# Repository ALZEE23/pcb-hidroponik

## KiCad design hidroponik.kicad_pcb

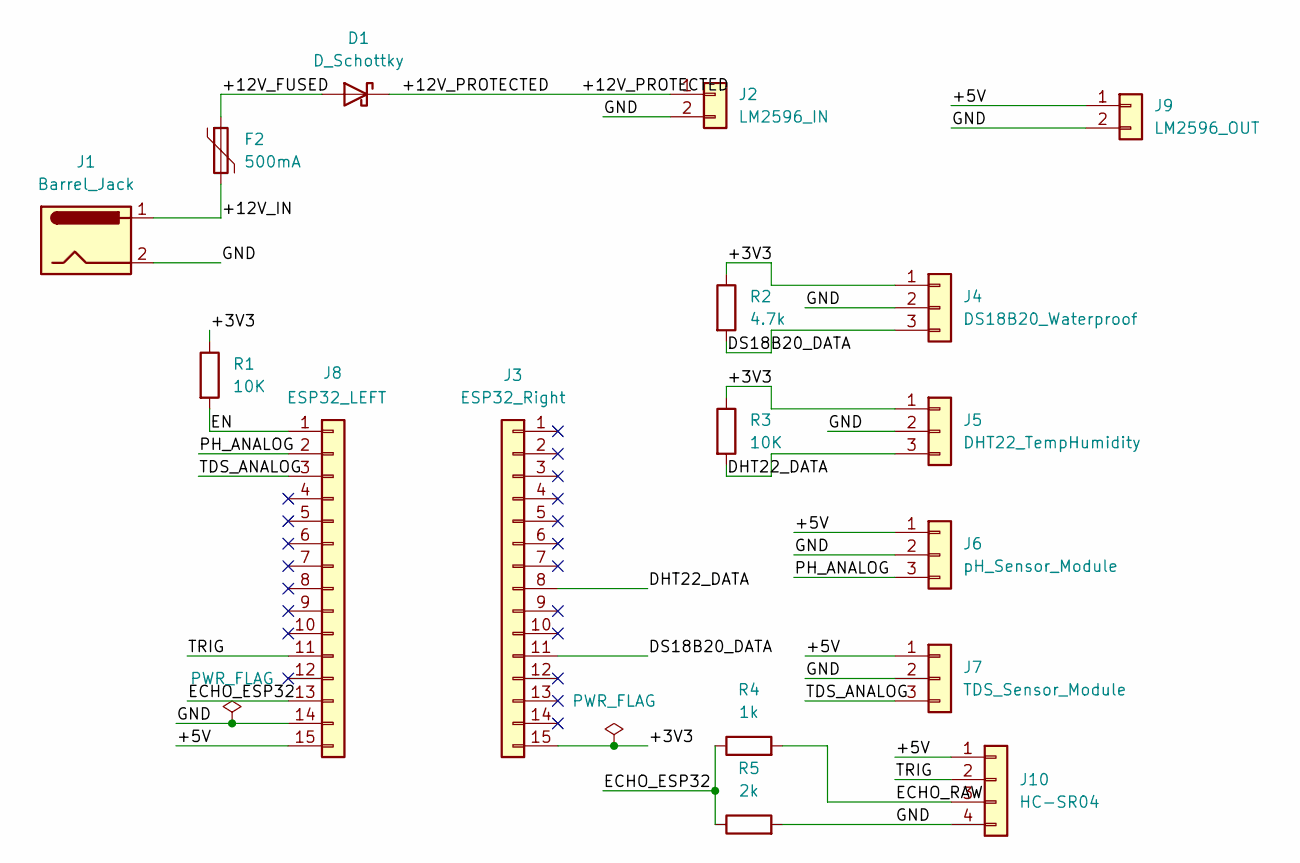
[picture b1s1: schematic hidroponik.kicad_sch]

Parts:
D1: D_Schottky; D_DO-41_SOD81_P10.16mm_Horizontal
F2: 500mA; Fuse_Bourns_MF-RG300
J1: Barrel_Jack; BarrelJack_CUI_PJ-102AH_Horizontal
J2: LM2596_IN; PinHeader_1x02_P2.54mm_Vertical
J3: ESP32_Right; PinSocket_1x15_P2.54mm_Vertical
J4: DS18B20_Waterproof; PinHeader_1x03_P2.54mm_Vertical
J5: DHT22_TempHumidity; PinHeader_1x03_P2.54mm_Vertical
J6: pH_Sensor_Module; PinHeader_1x03_P2.54mm_Vertical
J7: TDS_Sensor_Module; PinHeader_1x03_P2.54mm_Vertical
J8: ESP32_LEFT; PinSocket_1x15_P2.54mm_Vertical
J9: LM2596_OUT; PinHeader_1x02_P2.54mm_Vertical
J10: HC-SR04; PinHeader_1x04_P2.54mm_Vertical
R1, R3: 10K; R_Axial_DIN0207_L6.3mm_D2.5mm_P10.16mm_Horizontal
R2: 4.7k; R_Axial_DIN0207_L6.3mm_D2.5mm_P10.16mm_Horizontal
R4: 1k; R_Axial_DIN0207_L6.3mm_D2.5mm_P10.16mm_Horizontal
R5: 2k; R_Axial_DIN0207_L6.3mm_D2.5mm_P10.16mm_Horizontal

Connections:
/+3V3: J3.15, J4.1, J5.1, R1.1, R2.1, R3.1
/+5V: J6.1, J7.1, J8.15, J9.1, J10.1
/+12V_FUSED: D1.2 (A), F2.1
/+12V_IN: F2.2, J1.1
/+12V_PROTECTED: D1.1 (K), J2.1
/DHT22_DATA: J3.8, J5.3, R3.2
/DS18B20_DATA: J3.11, J4.3, R2.2
/ECHO_ESP32: J8.13, R4.1, R5.1
/ECHO_RAW: J10.3, R4.2
/EN: J8.1, R1.2
/GND: J1.2, J2.2, J4.2, J5.2, J6.2, J7.2, J8.14, J9.2, J10.4, R5.2
/PH_ANALOG: J6.3, J8.2
/TDS_ANALOG: J7.3, J8.3
/TRIG: J8.11, J10.2

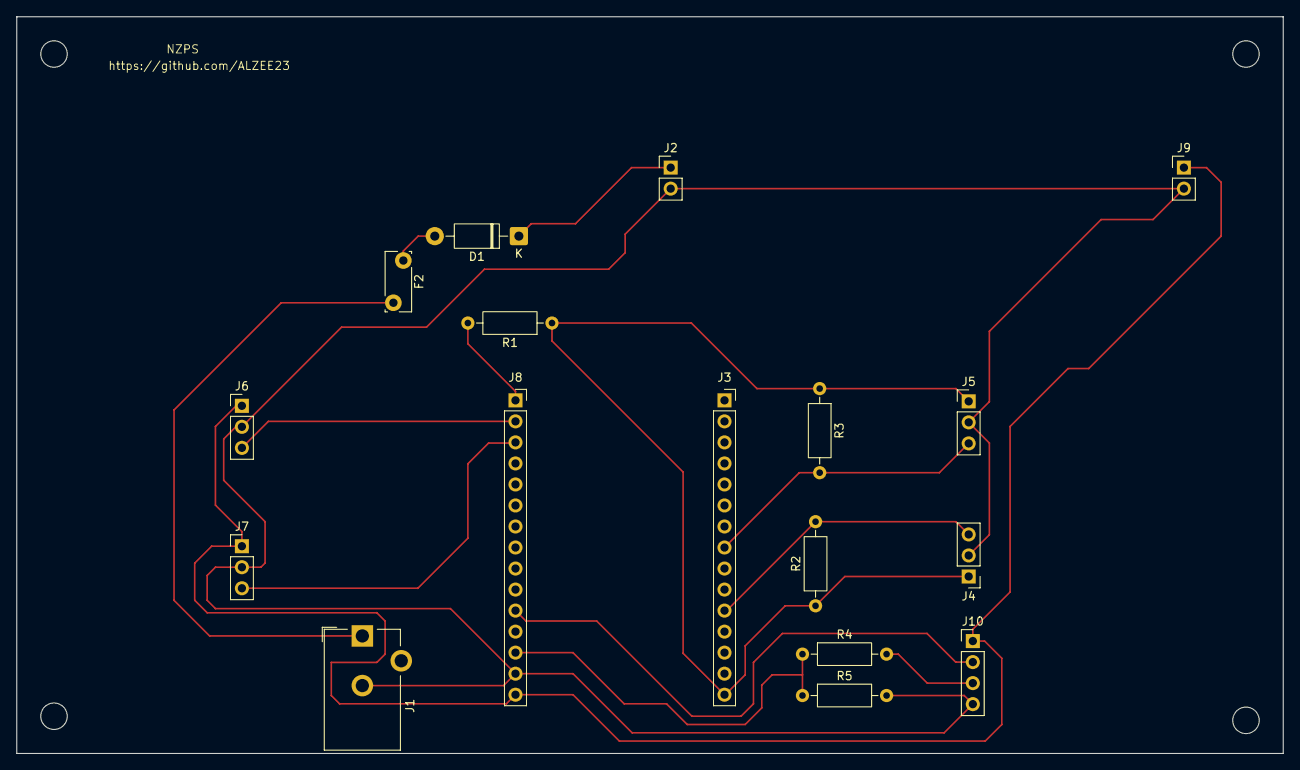
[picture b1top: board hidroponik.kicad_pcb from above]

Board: 2 copper layers, 153.0 x 89.0 mm, 17 parts (0 on the bottom side), 14 nets.
